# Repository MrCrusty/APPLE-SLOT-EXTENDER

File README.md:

# Apple 2 & 2e slot extender
# I will start off by saying that this is my first time posting a GitHub project and also the first time I have had a PCB fabricated commercially.
## Why do I want an Apple 2 or 2e slot extender?
### Its very tight and dark to probe a card inside the case of a Vintage Apple 2e computer, especially as there are a lot of bare live parts that can be contacted or shorted inside the case and on the Apple mother board.
Thus getting the card under test outside the case is a must for keeping my Apple well and running into the next decade.
Apple Card extenders are hard to source at the moment in the year 2025, so I decided to have a go at making my own.

I have used Kicad 9 to design the passive circuit and produce the PCB.

Not all of the design is my work as I asked contributor markdev if I could use one of his card edge footprints. And you can see his very kind reply agreeing to my use of his hard work.

*Hey there, yes that would be OK. The footprint is in this file https://github.com/markadev/AppleII-VGA/blob/main/AppleVGA/AppleVGA.pretty/AppleIIBus_Edge.kicad_mod which you can copy into your own project.
I also have another footprint in this library: https://github.com/markadev/KiCad-AppleII HOWEVER it contains some small size adjustments from the one used in this project and I never got around to creating a board to test it. So it's a bit more of a risk to use.*
 
My first PCB has worked but it seems that I have used the footprint that required some adjustment. 

### It’ s pictured below and was fabricated by PCBWAY directly from the Kicad project.

The center slots are to allow simple seperation with a hacksaw so that the two halves can then be joined with a 50 way ribbon cable.

As stated the card edge is not quite as snug in the Apple slot as it should be so a Version 2 was designed with the card edge suitably adjusted to fit the Apple slot size snugly.
I had during the above production of Version 1 shown the 3D design to the subscribers at APPLEFRITTER.com and asked for any improvements that might be made to Version 1. I had two answers 

The first was to suggest the use of Electroless Nickel Immersion Gold (ENIG) instead of tin.

## Version 2 nearly stalled at this point as it would seem that I must have had a first time deal from PCBWAY. The cost of the PCB had increased three times over Version 1 and the postage had jumped to the highest rate with no other options, if I was to request ENIG my wife would have have had me on bread and water for a month.

I decided to have a trawl on the web and see if other companies offered better deals 
## AISLER has come to my rescue offering a resonable PCB production cost downloaded direct from my Kicad project with resonable postage rates from Germany to the UK. ENIG was 3 Euro more than tin. Version 2 arrived exactly on the day that they advised and emails during the production run kept me informed of progress. 
## Version 2 meets the card edge requirements I expected and is nice and snug fit in the card socket.

## I said there was a second suggestion which was to have a silkscreen with names of the contacts related to the extension slot, this request arrived just after Version 2 had been sent for production. 
## A Version 3 has been designed with the new silk screen and components adjusted to allow the the extended size of the silk screen, its not been sent for production but uses exactly the same edge connector as Version 2.

# On the subject of downloading the Kicad 9 project files.
## If you just want to have a copy of the project files CLICK ON THE GREEN BUTTON and select "download zip" option this will give you all the files and pictures in this repository, pictures are large in bytes, so I tend to delete when I have the unzipped file on my local machine. 
### If you want to Fork this project be my guest. 
### I do not intend to sell these cards myself but if you want to manufacture for sale please make sure you donate to Kicad.

# Please be aware you can plug a card in back to front with terrible results to the card and the Apple computer so do take care when using the extender. 
# LIKE ALL MY PROJECTS ITS FREE TO USE AND ABUSE, BUT I DO NOT TAKE RESPONSIBILITY THAT YOU APPLE COMPUTER WILL LIKE OR BE ABLE TO USE THIS EXTENDER. MINE IS HAPPY WITH IT YOURS MAY NOT BE> 
Some previous web discussion with regard to cable extenders suggest they cause timing problems. 
At the bus speed of the Apple if you get this problem then you probably have a design problem on the card anyway, how ever the ribbon cable may generate crosstalk as each active ribbon cable is not seperated by a ground line.

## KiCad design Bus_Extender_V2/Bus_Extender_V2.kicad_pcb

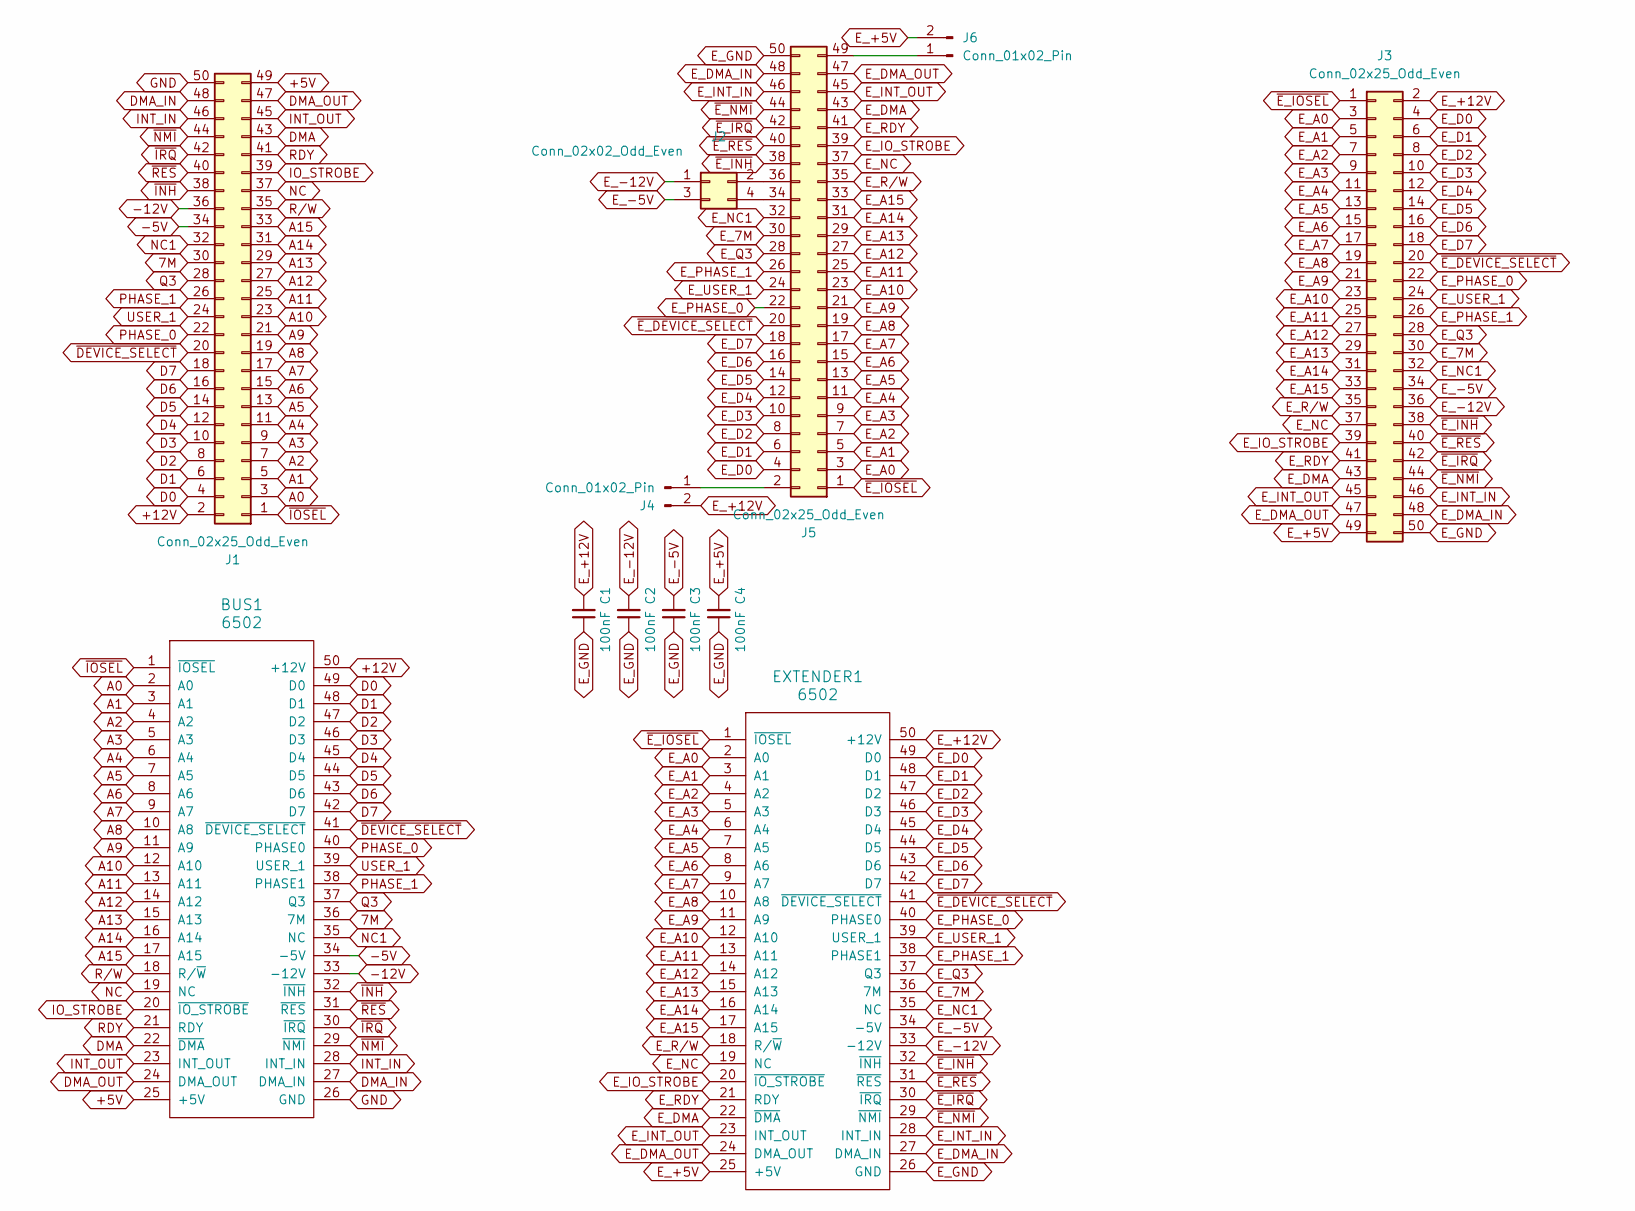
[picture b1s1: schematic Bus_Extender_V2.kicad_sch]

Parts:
BUS1: 6502; AppleIIBus_Edge_65.70
C1, C2, C3, C4: 100nF; C_Disc_D4.3mm_W1.9mm_P5.00mm
EXTENDER1: 6502; BUS_6502_v1
J1: Conn_02x25_Odd_Even; IDC-Header_2x25_P2.54mm_Horizontal
J2: Conn_02x02_Odd_Even; PinHeader_2x02_P2.54mm_Vertical
J3: Conn_02x25_Odd_Even; PinSocket_2x25_P2.54mm_Vertical
J4, J6: Conn_01x02_Pin; PinHeader_1x02_P2.54mm_Vertical
J5: Conn_02x25_Odd_Even; IDC-Header_2x25_P2.54mm_Vertical

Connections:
7M: BUS1.36 (7M), J1.30
+5V: BUS1.25 (+5V), J1.49
+12V: BUS1.50 (+12V), J1.2
-5V: BUS1.34 (-5V), J1.34
-12V: BUS1.33 (-12V), J1.36
A0: BUS1.2 (A0), J1.3
A1: BUS1.3 (A1), J1.5
A2: BUS1.4 (A2), J1.7
A3: BUS1.5 (A3), J1.9
A4: BUS1.6 (A4), J1.11
A5: BUS1.7 (A5), J1.13
A6: BUS1.8 (A6), J1.15
A7: BUS1.9 (A7), J1.17
A8: BUS1.10 (A8), J1.19
A9: BUS1.11 (A9), J1.21
A10: BUS1.12 (A10), J1.23
A11: BUS1.13 (A11), J1.25
A12: BUS1.14 (A12), J1.27
A13: BUS1.15 (A13), J1.29
A14: BUS1.16 (A14), J1.31
A15: BUS1.17 (A15), J1.33
D0: BUS1.49 (D0), J1.4
D1: BUS1.48 (D1), J1.6
D2: BUS1.47 (D2), J1.8
D3: BUS1.46 (D3), J1.10
D4: BUS1.45 (D4), J1.12
D5: BUS1.44 (D5), J1.14
D6: BUS1.43 (D6), J1.16
D7: BUS1.42 (D7), J1.18
DMA: BUS1.22 (~DMA), J1.43
DMA_IN: BUS1.27 (DMA_IN), J1.48
DMA_OUT: BUS1.24 (DMA_OUT), J1.47
E_7M: EXTENDER1.36 (7M), J3.30, J5.30
E_+5V: C4.2, EXTENDER1.25 (+5V), J3.49, J6.2
E_+12V: C1.2, EXTENDER1.50 (+12V), J3.2, J4.2
E_-5V: C3.2, EXTENDER1.34 (-5V), J2.3, J3.34
E_-12V: C2.2, EXTENDER1.33 (-12V), J2.1, J3.36
E_A0: EXTENDER1.2 (A0), J3.3, J5.3
E_A1: EXTENDER1.3 (A1), J3.5, J5.5
E_A2: EXTENDER1.4 (A2), J3.7, J5.7
E_A3: EXTENDER1.5 (A3), J3.9, J5.9
E_A4: EXTENDER1.6 (A4), J3.11, J5.11
E_A5: EXTENDER1.7 (A5), J3.13, J5.13
E_A6: EXTENDER1.8 (A6), J3.15, J5.15
E_A7: EXTENDER1.9 (A7), J3.17, J5.17
E_A8: EXTENDER1.10 (A8), J3.19, J5.19
E_A9: EXTENDER1.11 (A9), J3.21, J5.21
E_A10: EXTENDER1.12 (A10), J3.23, J5.23
E_A11: EXTENDER1.13 (A11), J3.25, J5.25
E_A12: EXTENDER1.14 (A12), J3.27, J5.27
E_A13: EXTENDER1.15 (A13), J3.29, J5.29
E_A14: EXTENDER1.16 (A14), J3.31, J5.31
E_A15: EXTENDER1.17 (A15), J3.33, J5.33
E_D0: EXTENDER1.49 (D0), J3.4, J5.4
E_D1: EXTENDER1.48 (D1), J3.6, J5.6
E_D2: EXTENDER1.47 (D2), J3.8, J5.8
E_D3: EXTENDER1.46 (D3), J3.10, J5.10
E_D4: EXTENDER1.45 (D4), J3.12, J5.12
E_D5: EXTENDER1.44 (D5), J3.14, J5.14
E_D6: EXTENDER1.43 (D6), J3.16, J5.16
E_D7: EXTENDER1.42 (D7), J3.18, J5.18
E_DMA: EXTENDER1.22 (~DMA), J3.43, J5.43
E_DMA_IN: EXTENDER1.27 (DMA_IN), J3.48, J5.48
E_DMA_OUT: EXTENDER1.24 (DMA_OUT), J3.47, J5.47
E_GND: C1.1, C2.1, C3.1, C4.1, EXTENDER1.26 (GND), J3.50, J5.50
E_INT_IN: EXTENDER1.28 (INT_IN), J3.46, J5.46
E_INT_OUT: EXTENDER1.23 (INT_OUT), J3.45, J5.45
E_IO_STROBE: EXTENDER1.20 (~IO_STROBE), J3.39, J5.39
E_NC: EXTENDER1.19 (NC), J3.37, J5.37
E_NC1: EXTENDER1.35 (NC), J3.32, J5.32
E_PHASE_0: EXTENDER1.40 (PHASE0), J3.22, J5.22
E_PHASE_1: EXTENDER1.38 (PHASE1), J3.26, J5.26
E_Q3: EXTENDER1.37 (Q3), J3.28, J5.28
E_RDY: EXTENDER1.21 (RDY), J3.41, J5.41
E_R/W: EXTENDER1.18 (R/~W), J3.35, J5.35
E_USER_1: EXTENDER1.39 (USER_1), J3.24, J5.24
GND: BUS1.26 (GND), J1.50
INT_IN: BUS1.28 (INT_IN), J1.46
INT_OUT: BUS1.23 (INT_OUT), J1.45
IO_STROBE: BUS1.20 (~IO_STROBE), J1.39
NC: BUS1.19 (NC), J1.37
NC1: BUS1.35 (NC), J1.32
unnamed: J2.2, J5.36
unnamed: J2.4, J5.34
unnamed: J4.1, J5.2
unnamed: J5.49, J6.1
PHASE_0: BUS1.40 (PHASE0), J1.22
PHASE_1: BUS1.38 (PHASE1), J1.26
Q3: BUS1.37 (Q3), J1.28
RDY: BUS1.21 (RDY), J1.41
R/W: BUS1.18 (R/~W), J1.35
USER_1: BUS1.39 (USER_1), J1.24
~DEVICE_SELECT: BUS1.41 (~DEVICE_SELECT), J1.20
~E_DEVICE_SELECT: EXTENDER1.41 (~DEVICE_SELECT), J3.20, J5.20
~E_INH: EXTENDER1.32 (~INH), J3.38, J5.38
~E_IOSEL: EXTENDER1.1 (~IOSEL), J3.1, J5.1
~E_IRQ: EXTENDER1.30 (~IRQ), J3.42, J5.42
~E_NMI: EXTENDER1.29 (~NMI), J3.44, J5.44
~E_RES: EXTENDER1.31 (~RES), J3.40, J5.40
~INH: BUS1.32 (~INH), J1.38
~IOSEL: BUS1.1 (~IOSEL), J1.1
~IRQ: BUS1.30 (~IRQ), J1.42
~NMI: BUS1.29 (~NMI), J1.44
~RES: BUS1.31 (~RES), J1.40

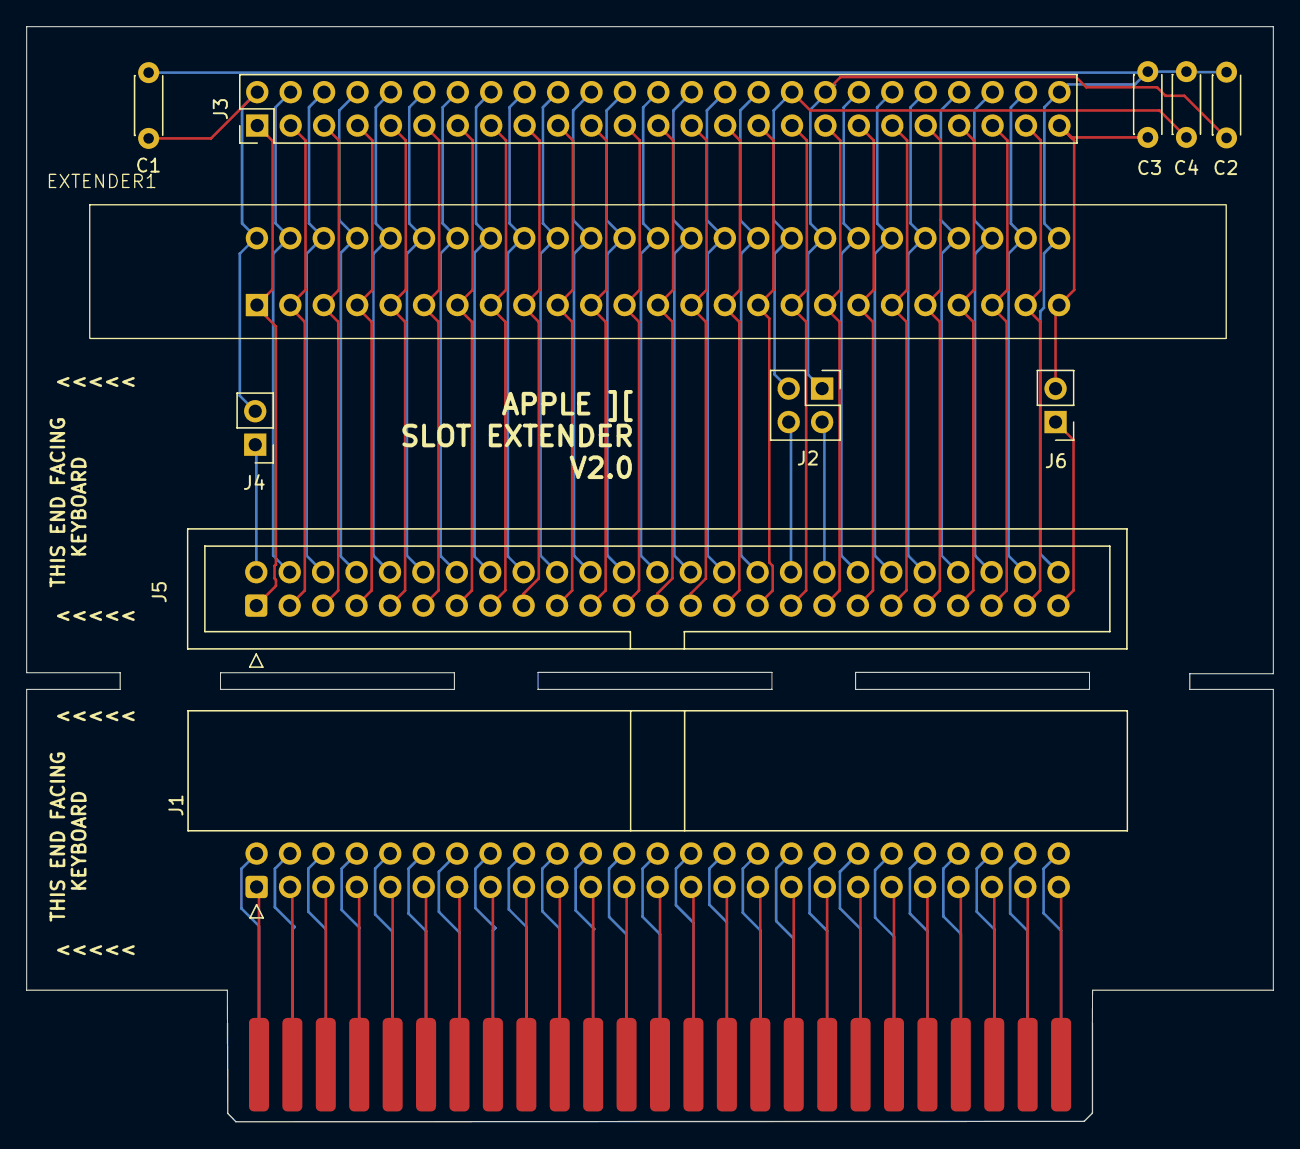
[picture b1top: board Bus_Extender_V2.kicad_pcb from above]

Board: 2 copper layers, 94.7 x 83.2 mm, 12 parts (0 on the bottom side), 104 nets.

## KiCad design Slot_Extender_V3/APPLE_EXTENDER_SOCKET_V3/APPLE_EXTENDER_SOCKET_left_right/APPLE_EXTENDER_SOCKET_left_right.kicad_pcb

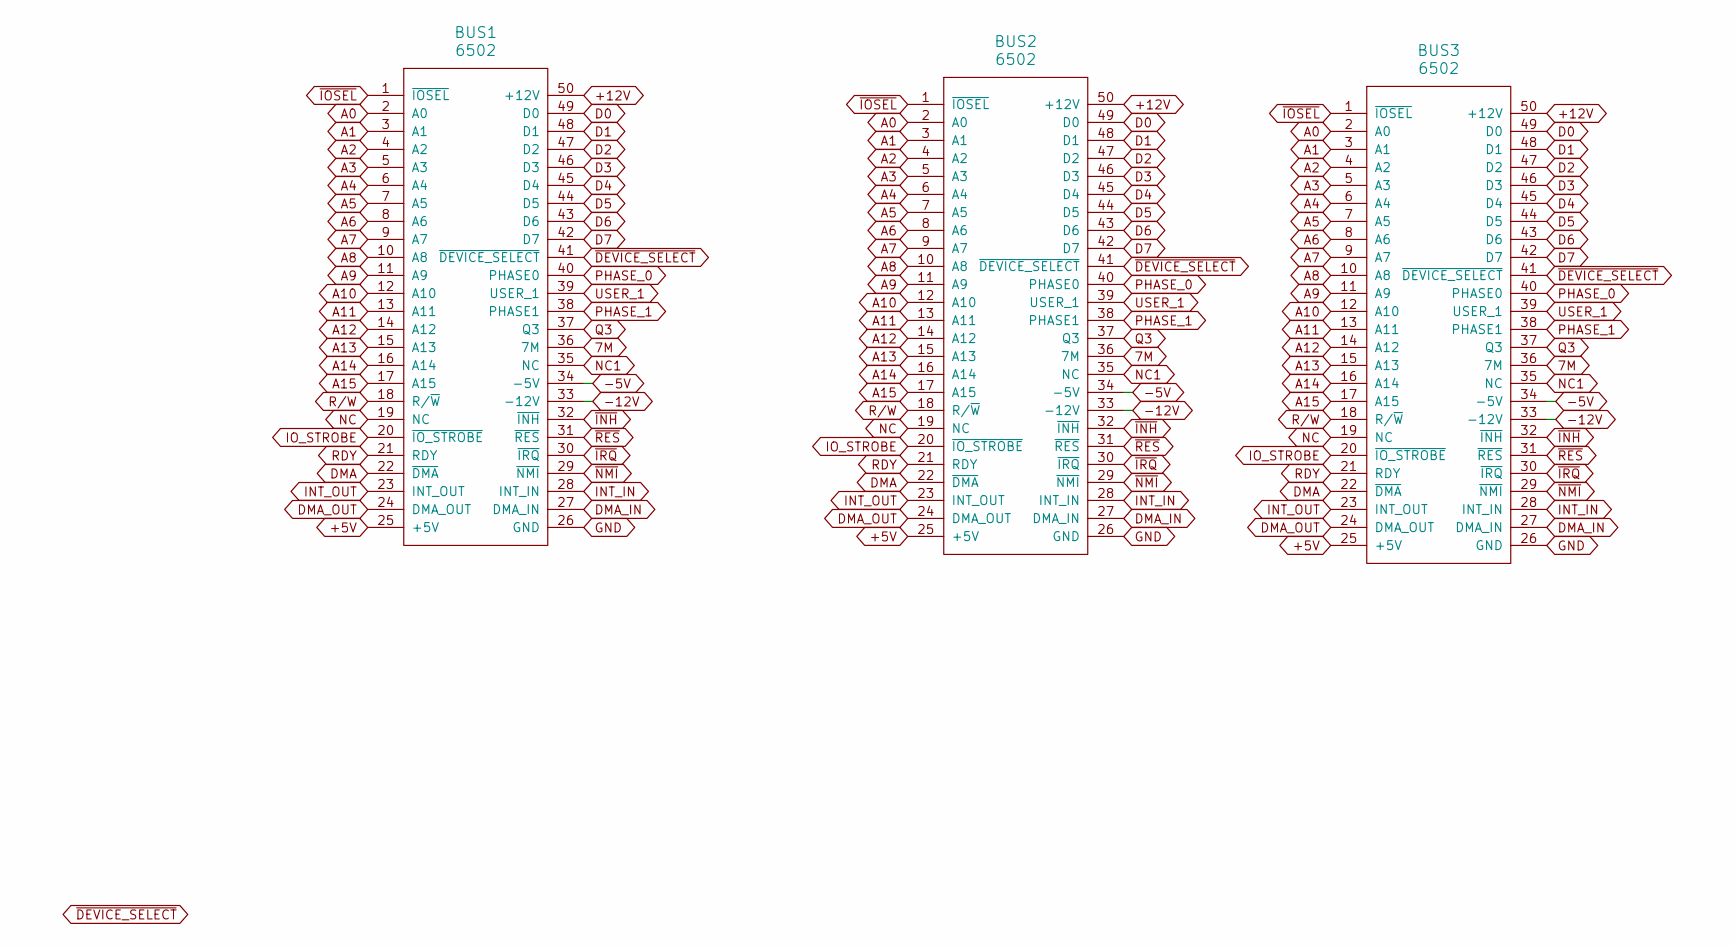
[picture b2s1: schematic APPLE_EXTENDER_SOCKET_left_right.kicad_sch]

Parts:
BUS1: 6502; AppleIIBus_Edge_65.70
BUS2, BUS3: 6502; BUS_6502_v1

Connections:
7M: BUS1.36 (7M), BUS2.36 (7M), BUS3.36 (7M)
+5V: BUS1.25 (+5V), BUS2.25 (+5V), BUS3.25 (+5V)
+12V: BUS1.50 (+12V), BUS2.50 (+12V), BUS3.50 (+12V)
-5V: BUS1.34 (-5V), BUS2.34 (-5V), BUS3.34 (-5V)
-12V: BUS1.33 (-12V), BUS2.33 (-12V), BUS3.33 (-12V)
A0: BUS1.2 (A0), BUS2.2 (A0), BUS3.2 (A0)
A1: BUS1.3 (A1), BUS2.3 (A1), BUS3.3 (A1)
A2: BUS1.4 (A2), BUS2.4 (A2), BUS3.4 (A2)
A3: BUS1.5 (A3), BUS2.5 (A3), BUS3.5 (A3)
A4: BUS1.6 (A4), BUS2.6 (A4), BUS3.6 (A4)
A5: BUS1.7 (A5), BUS2.7 (A5), BUS3.7 (A5)
A6: BUS1.8 (A6), BUS2.8 (A6), BUS3.8 (A6)
A7: BUS1.9 (A7), BUS2.9 (A7), BUS3.9 (A7)
A8: BUS1.10 (A8), BUS2.10 (A8), BUS3.10 (A8)
A9: BUS1.11 (A9), BUS2.11 (A9), BUS3.11 (A9)
A10: BUS1.12 (A10), BUS2.12 (A10), BUS3.12 (A10)
A11: BUS1.13 (A11), BUS2.13 (A11), BUS3.13 (A11)
A12: BUS1.14 (A12), BUS2.14 (A12), BUS3.14 (A12)
A13: BUS1.15 (A13), BUS2.15 (A13), BUS3.15 (A13)
A14: BUS1.16 (A14), BUS2.16 (A14), BUS3.16 (A14)
A15: BUS1.17 (A15), BUS2.17 (A15), BUS3.17 (A15)
D0: BUS1.49 (D0), BUS2.49 (D0), BUS3.49 (D0)
D1: BUS1.48 (D1), BUS2.48 (D1), BUS3.48 (D1)
D2: BUS1.47 (D2), BUS2.47 (D2), BUS3.47 (D2)
D3: BUS1.46 (D3), BUS2.46 (D3), BUS3.46 (D3)
D4: BUS1.45 (D4), BUS2.45 (D4), BUS3.45 (D4)
D5: BUS1.44 (D5), BUS2.44 (D5), BUS3.44 (D5)
D6: BUS1.43 (D6), BUS2.43 (D6), BUS3.43 (D6)
D7: BUS1.42 (D7), BUS2.42 (D7), BUS3.42 (D7)
DMA: BUS1.22 (~DMA), BUS2.22 (~DMA), BUS3.22 (~DMA)
DMA_IN: BUS1.27 (DMA_IN), BUS2.27 (DMA_IN), BUS3.27 (DMA_IN)
DMA_OUT: BUS1.24 (DMA_OUT), BUS2.24 (DMA_OUT), BUS3.24 (DMA_OUT)
GND: BUS1.26 (GND), BUS2.26 (GND), BUS3.26 (GND)
INT_IN: BUS1.28 (INT_IN), BUS2.28 (INT_IN), BUS3.28 (INT_IN)
INT_OUT: BUS1.23 (INT_OUT), BUS2.23 (INT_OUT), BUS3.23 (INT_OUT)
IO_STROBE: BUS1.20 (~IO_STROBE), BUS2.20 (~IO_STROBE), BUS3.20 (~IO_STROBE)
NC: BUS1.19 (NC), BUS2.19 (NC), BUS3.19 (NC)
NC1: BUS1.35 (NC), BUS2.35 (NC), BUS3.35 (NC)
PHASE_0: BUS1.40 (PHASE0), BUS2.40 (PHASE0), BUS3.40 (PHASE0)
PHASE_1: BUS1.38 (PHASE1), BUS2.38 (PHASE1), BUS3.38 (PHASE1)
Q3: BUS1.37 (Q3), BUS2.37 (Q3), BUS3.37 (Q3)
RDY: BUS1.21 (RDY), BUS2.21 (RDY), BUS3.21 (RDY)
R/W: BUS1.18 (R/~W), BUS2.18 (R/~W), BUS3.18 (R/~W)
USER_1: BUS1.39 (USER_1), BUS2.39 (USER_1), BUS3.39 (USER_1)
~DEVICE_SELECT: BUS1.41 (~DEVICE_SELECT), BUS2.41 (~DEVICE_SELECT), BUS3.41 (~DEVICE_SELECT)
~INH: BUS1.32 (~INH), BUS2.32 (~INH), BUS3.32 (~INH)
~IOSEL: BUS1.1 (~IOSEL), BUS2.1 (~IOSEL), BUS3.1 (~IOSEL)
~IRQ: BUS1.30 (~IRQ), BUS2.30 (~IRQ), BUS3.30 (~IRQ)
~NMI: BUS1.29 (~NMI), BUS2.29 (~NMI), BUS3.29 (~NMI)
~RES: BUS1.31 (~RES), BUS2.31 (~RES), BUS3.31 (~RES)

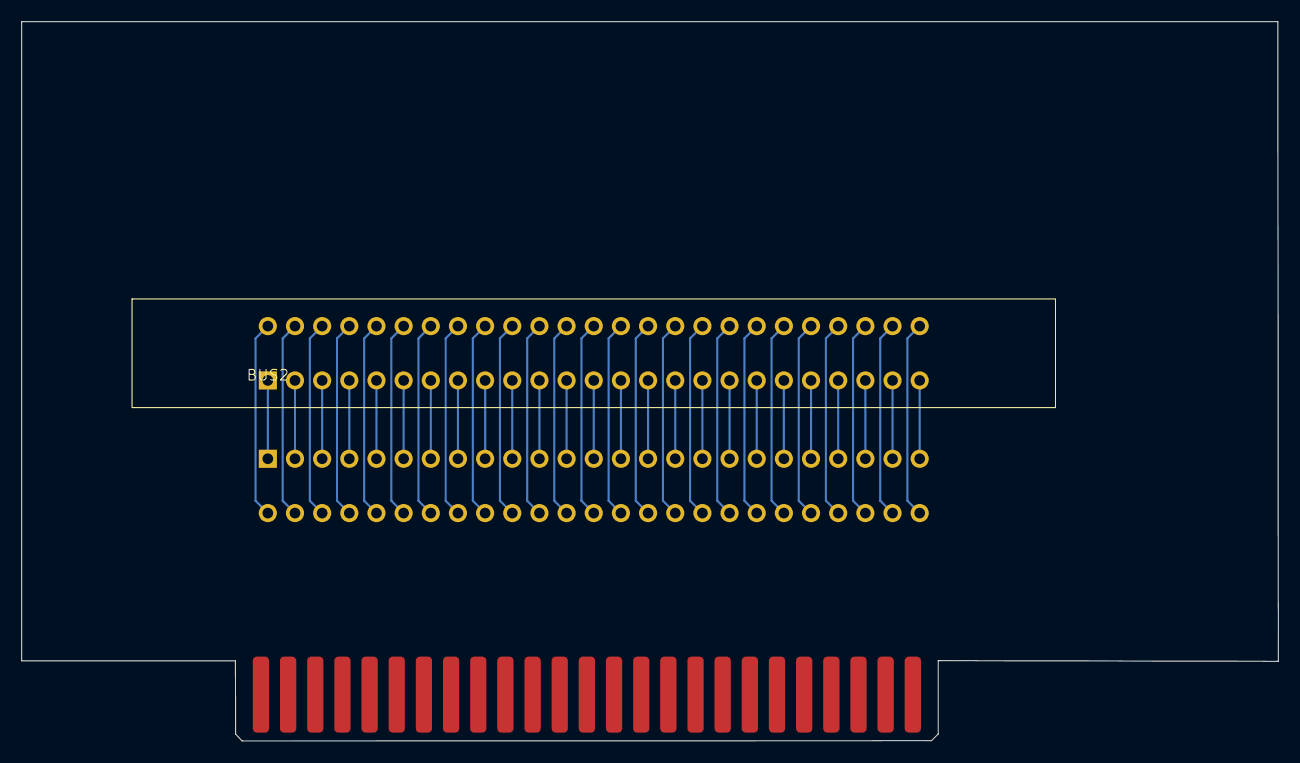
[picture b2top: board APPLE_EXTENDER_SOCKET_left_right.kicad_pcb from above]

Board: 2 copper layers, 117.5 x 67.3 mm, 3 parts (1 on the bottom side), 50 nets.

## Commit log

2025-08-16 removed items
    wrong files added
